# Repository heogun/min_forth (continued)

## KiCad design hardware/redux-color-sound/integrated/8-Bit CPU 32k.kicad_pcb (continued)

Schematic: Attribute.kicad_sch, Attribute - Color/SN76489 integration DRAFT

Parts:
R37, R38, R39, R40, R41: 470; R_Axial_DIN0207_L6.3mm_D2.5mm_P7.62mm_Horizontal
R42: 33; R_Axial_DIN0207_L6.3mm_D2.5mm_P7.62mm_Horizontal
U66: 74HC574; DIP-20_W7.62mm_Socket
U68: 74AC08; DIP-14_W7.62mm_Socket
U77: AS6C62256-55PCN ATTRIBUTE; DIP-28_W15.24mm_Socket
U78: 74HC283; DIP-16_W7.62mm_Socket
U79: 74HC86; DIP-14_W7.62mm_Socket
U80: 74HC245; DIP-20_W7.62mm_Socket
U81: 74HCT377; DIP-20_W7.62mm_Socket
U82: 74HC74; DIP-14_W7.62mm_Socket

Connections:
16MHz: U68.1, U68.2; also elsewhere on the board
+5V: U66.20 (VCC), U68.14 (VCC), U77.28 (VCC), U78.16 (VCC), U79.10, U79.14 (VCC), U80.1 (A->B), U80.20 (VCC), U81.20 (VCC), U82.4 (~S), U82.10 (~S), U82.14 (VCC); also elsewhere on the board
A9: U66.2 (D0); also elsewhere on the board
A10: U66.3 (D1); also elsewhere on the board
A11: U66.4 (D2); also elsewhere on the board
A12: U66.5 (D3); also elsewhere on the board
A13: U66.6 (D4); also elsewhere on the board
CS_16MHZ_DRV: R42.1, U68.3
CS_ACTIVE_LATCH: U79.9; also elsewhere on the board
CS_ATTR_D0: U77.11 (I/O0), U80.18 (B0), U81.3 (D0)
CS_ATTR_D1: U77.12 (I/O1), U80.17 (B1), U81.4 (D1)
CS_ATTR_D2: U77.13 (I/O2), U80.16 (B2), U81.7 (D2)
CS_ATTR_D3: U77.15 (I/O3), U80.15 (B3), U81.8 (D3)
CS_ATTR_D4: U77.16 (I/O4), U80.14 (B4), U81.13 (D4)
CS_ATTR_D5: U77.17 (I/O5), U80.13 (B5), U81.14 (D5)
CS_ATTR_D6: U77.18 (I/O6), U80.12 (B6), U81.17 (D6)
CS_ATTR_D7: U77.19 (I/O7), U80.11 (B7), U81.18 (D7)
CS_ATTR_MODE: U82.2 (D); also elsewhere on the board
CS_ATTR_Q0: U81.2 (Q0); also elsewhere on the board
CS_ATTR_Q1: U81.5 (Q1); also elsewhere on the board
CS_ATTR_Q2: U81.6 (Q2); also elsewhere on the board
CS_ATTR_Q3: U81.9 (Q3); also elsewhere on the board
CS_ATTR_Q4: U81.12 (Q4); also elsewhere on the board
CS_ATTR_Q5: U81.15 (Q5); also elsewhere on the board
CS_ATTR_Q6: U81.16 (Q6); also elsewhere on the board
CS_ATTR_Q7: U81.19 (Q7); also elsewhere on the board
CS_ATTR_WE_N: U77.27 (~WE); also elsewhere on the board
CS_CA6: R37.2, U66.19 (Q0), U77.4 (A6)
CS_CA7: R38.2, U66.18 (Q1), U77.3 (A7)
CS_CA8: R39.2, U66.17 (Q2), U77.25 (A8)
CS_CA9: R40.2, U66.16 (Q3), U77.24 (A9)
CS_CA10: R41.2, U66.15 (Q4), U77.21 (A10)
CS_EXT_16MHZ: R42.2, U81.11 (CP); also elsewhere on the board
CS_PENDING_ATTR: U82.5 (Q); also elsewhere on the board
CS_PENDING_BITMAP: U82.6 (~Q); also elsewhere on the board
CS_RGB_BLANK: U79.8; also elsewhere on the board
CS_ROW_CARRY: U78.9 (C4), U79.1
CS_SCA6: R37.1, U78.4 (S1)
CS_SCA7: R38.1, U78.1 (S2); also elsewhere on the board
CS_SCA8: R39.1, U78.13 (S3); also elsewhere on the board
CS_SCA9: R40.1, U78.10 (S4); also elsewhere on the board
CS_SCA10: R41.1, U79.3; also elsewhere on the board
CS_V4: U78.7 (C0); also elsewhere on the board
CS_V8: U78.5 (A1); also elsewhere on the board
CS_V16: U78.3 (A2); also elsewhere on the board
CS_V32: U78.14 (A3); also elsewhere on the board
CS_V64: U78.12 (A4); also elsewhere on the board
CS_V128: U79.2; also elsewhere on the board
CS_VA0: U77.10 (A0); also elsewhere on the board
CS_VA1: U77.9 (A1); also elsewhere on the board
CS_VA2: U77.8 (A2); also elsewhere on the board
CS_VA3: U77.7 (A3); also elsewhere on the board
CS_VA4: U77.6 (A4); also elsewhere on the board
CS_VA5: U77.5 (A5); also elsewhere on the board
CS_VDATA0: U80.2 (A0); also elsewhere on the board
CS_VDATA1: U80.3 (A1); also elsewhere on the board
CS_VDATA2: U80.4 (A2); also elsewhere on the board
CS_VDATA3: U80.5 (A3); also elsewhere on the board
CS_VDATA4: U80.6 (A4); also elsewhere on the board
CS_VDATA5: U80.7 (A5); also elsewhere on the board
CS_VDATA6: U80.8 (A6); also elsewhere on the board
CS_VDATA7: U80.9 (A7); also elsewhere on the board
CS_VREG_CP: U66.11 (Cp), U82.3 (C); also elsewhere on the board
GND: U66.7 (D5), U66.8 (D6), U66.9 (D7), U66.10 (GND), U68.4, U68.5, U68.7 (GND), U68.9, U68.10, U68.12, U68.13, U77.1 (A14), U77.2 (A12), U77.14 (GND), U77.20 (~CE), U77.23 (A11), U77.26 (A13), U78.2 (B2), U78.6 (B1), U78.8 (GND), U78.11 (B4), U78.15 (B3), U79.4, U79.5, U79.7 (GND), U79.12, U79.13, U80.10 (GND), U81.10 (GND), U82.7 (GND), U82.11 (C), U82.12 (D); also elsewhere on the board
~RESET: U82.1 (~R), U82.13 (~R); also elsewhere on the board
~VGA_GET: U77.22 (~OE), U81.1 (~E); also elsewhere on the board
~VREG_OE: U66.1 (OE), U80.19 (CE); also elsewhere on the board

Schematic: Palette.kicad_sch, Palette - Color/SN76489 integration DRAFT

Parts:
R28, R29: 750; R_Axial_DIN0207_L6.3mm_D2.5mm_P7.62mm_Horizontal
R30, R31, R32: 1.5k; R_Axial_DIN0207_L6.3mm_D2.5mm_P7.62mm_Horizontal
U83: 74HC173; DIP-16_W7.62mm_Socket
U84: 74HC08; DIP-14_W7.62mm_Socket
U85, U86: 74HC4002; DIP-14_W7.62mm_Socket
U87: 74HC30; DIP-14_W7.62mm_Socket
U88, U89: 74HC157; DIP-16_W7.62mm_Socket
U90: 74AC244; DIP-20_W7.62mm_Socket

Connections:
+5V: U83.16 (VCC), U84.14 (VCC), U85.14 (VDD), U86.14 (VDD), U87.6, U87.11, U87.12, U87.14 (VCC), U88.16 (VCC), U89.16 (VCC), U90.20 (VCC); also elsewhere on the board
CS_ACTIVE: U83.14 (D0), U86.13
CS_ACTIVE_LATCH: U83.3 (Q0); also elsewhere on the board
CS_ATTR_Q0: U88.3 (I1a); also elsewhere on the board
CS_ATTR_Q1: U88.6 (I1b); also elsewhere on the board
CS_ATTR_Q2: U88.10 (I1c); also elsewhere on the board
CS_ATTR_Q3: U88.13 (I1d); also elsewhere on the board
CS_ATTR_Q4: U88.2 (I0a); also elsewhere on the board
CS_ATTR_Q5: U88.5 (I0b); also elsewhere on the board
CS_ATTR_Q6: U88.11 (I0c); also elsewhere on the board
CS_ATTR_Q7: U88.14 (I0d); also elsewhere on the board
CS_B: U89.4 (Za), U90.11 (I0b)
CS_COLOR0: U88.4 (Za), U89.3 (I1a)
CS_COLOR1: U88.7 (Zb), U89.6 (I1b)
CS_COLOR2: U88.9 (Zc), U89.10 (I1c)
CS_COLOR3: U88.12 (Zd), U89.13 (I1d)
CS_COLOR_EN: U83.13 (D1); also elsewhere on the board
CS_COLOR_LATCH: U83.4 (Q1), U89.1 (S)
CS_DAC_B: R29.1, U90.9 (O0b)
CS_DAC_BI: R32.1, U90.7 (O1b)
CS_DAC_G: R28.1, U90.14 (O2a)
CS_DAC_GI: R31.1, U90.12 (O3a)
CS_DAC_R: U90.18 (O0a); also elsewhere on the board
CS_DAC_RI: R30.1, U90.16 (O1a)
CS_EXT_16MHZ: U83.7 (Cp); also elsewhere on the board
CS_G: U89.7 (Zb), U90.6 (I2a)
CS_H2: U87.5; also elsewhere on the board
CS_H4: U84.2, U87.4; also elsewhere on the board
CS_H8: U84.1, U87.3; also elsewhere on the board
CS_H12: U84.3, U85.11
CS_H16: U85.10, U87.2; also elsewhere on the board
CS_H32: U85.9, U87.1; also elsewhere on the board
CS_HHIGH_BAD: U86.1, U86.11
CS_HHIGH_OK: U86.2, U86.3, U86.4, U86.5, U87.8
CS_HLOW: U85.13, U86.10
CS_I: U89.12 (Zd), U90.4 (I1a), U90.8 (I3a), U90.13 (I1b)
CS_PIXEL: U88.1 (S), U89.2 (I0a), U89.5 (I0b), U89.11 (I0c), U89.14 (I0d); also elsewhere on the board
CS_R: U89.9 (Zc), U90.2 (I0a)
CS_RESET: U83.15 (Mr); also elsewhere on the board
CS_RGB_BLANK: U90.1 (OEa), U90.19 (OEb); also elsewhere on the board
CS_SCA7: U85.2; also elsewhere on the board
CS_SCA8: U85.3; also elsewhere on the board
CS_SCA9: U85.4; also elsewhere on the board
CS_SCA10: U85.5; also elsewhere on the board
CS_V256: U86.12; also elsewhere on the board
CS_VBAD: U85.1, U86.9
CS_VGA_B: R29.2, R32.2; also elsewhere on the board
CS_VGA_G: R28.2, R31.2; also elsewhere on the board
CS_VGA_R: R30.2; also elsewhere on the board
GND: U83.1 (Oe1), U83.2 (Oe2), U83.8 (GND), U83.10 (E2), U83.11 (D3), U83.12 (D2), U84.4, U84.5, U84.7 (GND), U84.9, U84.10, U84.12, U84.13, U85.7 (VSS), U85.12, U86.7 (VSS), U87.7 (GND), U88.8 (GND), U88.15 (E), U89.8 (GND), U89.15 (E), U90.10 (GND), U90.15 (I2b), U90.17 (I3b); also elsewhere on the board
~VGA_GET: U83.9 (E1); also elsewhere on the board

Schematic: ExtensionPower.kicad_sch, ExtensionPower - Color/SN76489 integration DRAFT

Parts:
C34, C35, C36, C37, C38, C39, C40, C41, C42, C44, C45, C46, C47, C48, C49, C50, C51, C52, C53, C54, C55, C56, C57, C58, C59, C60, C63: 100n; C_Disc_D5.0mm_W2.5mm_P2.50mm
C61: 10u 16V; CP_Radial_D5.0mm_P2.50mm

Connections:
+5V: C34.1, C35.1, C36.1, C37.1, C38.1, C39.1, C40.1, C41.1, C42.1, C44.1, C45.1, C46.1, C47.1, C48.1, C49.1, C50.1, C51.1, C52.1, C53.1, C54.1, C55.1, C56.1, C57.1, C58.1, C59.1, C60.1, C61.1, C63.1; also elsewhere on the board
GND: C34.2, C35.2, C36.2, C37.2, C38.2, C39.2, C40.2, C41.2, C42.2, C44.2, C45.2, C46.2, C47.2, C48.2, C49.2, C50.2, C51.2, C52.2, C53.2, C54.2, C55.2, C56.2, C57.2, C58.2, C59.2, C60.2, C61.2, C63.2; also elsewhere on the board

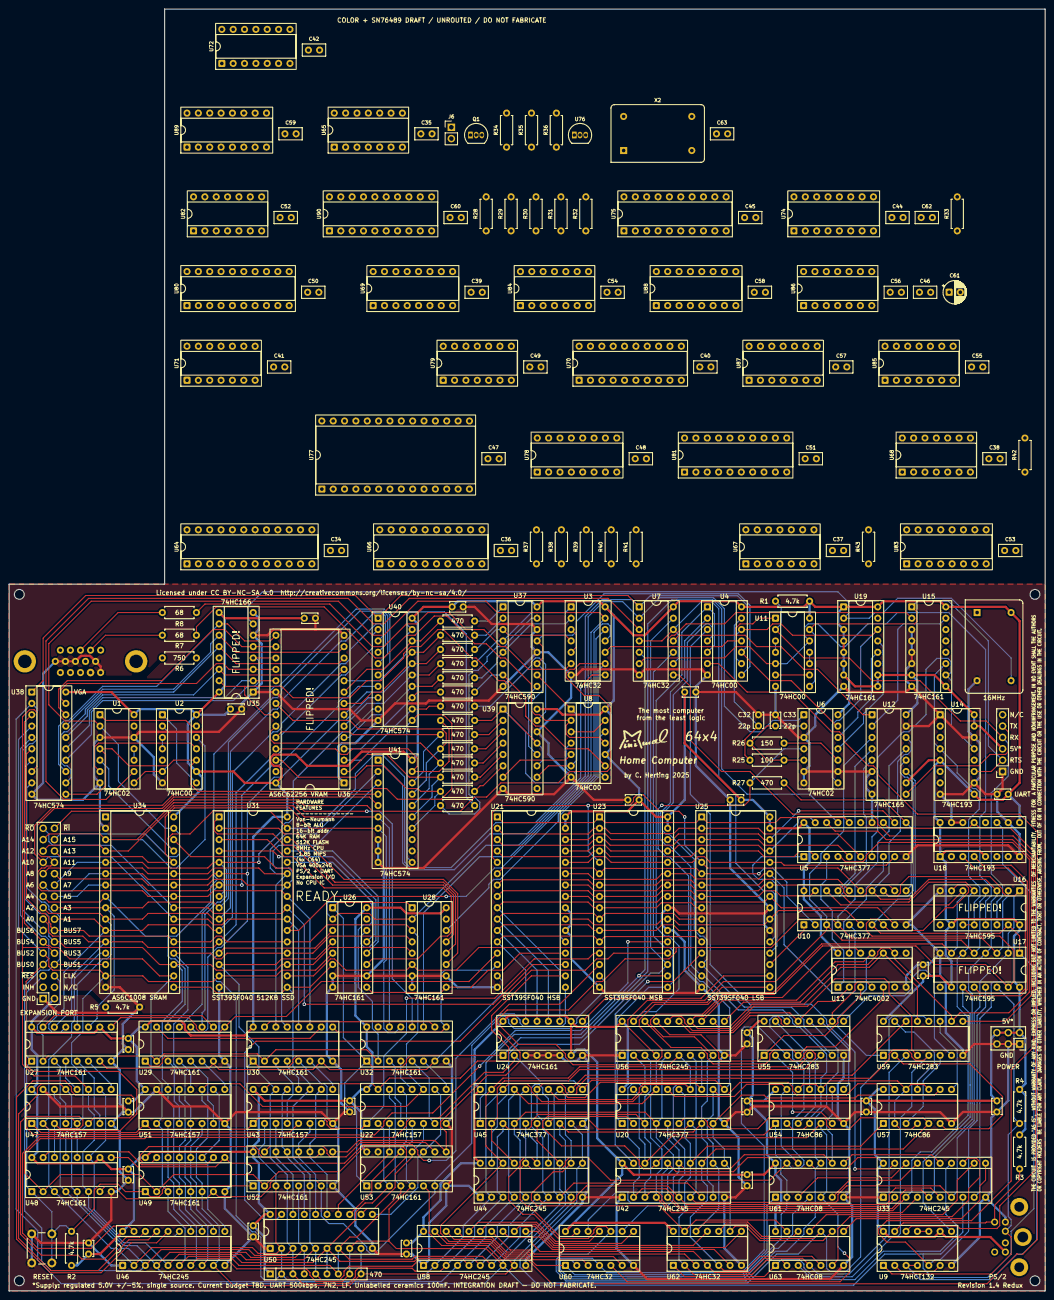
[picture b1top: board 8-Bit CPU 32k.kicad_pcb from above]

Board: 2 copper layers, 231.8 x 286.8 mm, 196 parts (0 on the bottom side), 348 nets.

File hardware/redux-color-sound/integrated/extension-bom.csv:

Reference,Value,Footprint,Schematic sheet
U64,ATF22V10C (CS_DECODE),Package_DIP:DIP-24_W7.62mm_Socket,ExtensionIO
U65,74HC04,Package_DIP:DIP-14_W7.62mm_Socket,ExtensionIO
U67,74HC02,Package_DIP:DIP-14_W7.62mm_Socket,ExtensionIO
U68,74AC08,Package_DIP:DIP-14_W7.62mm_Socket,Attribute
U69,74HC173,Package_DIP:DIP-16_W7.62mm_Socket,ExtensionIO
U70,74HC377,Package_DIP:DIP-20_W7.62mm_Socket,ExtensionIO
U71,74HC32,Package_DIP:DIP-14_W7.62mm_Socket,ExtensionIO
U72,74HC32,Package_DIP:DIP-14_W7.62mm_Socket,ExtensionIO
U74,SN76489AN,Package_DIP:DIP-16_W7.62mm_Socket,PSG
U75,74HCT244,Package_DIP:DIP-20_W7.62mm_Socket,PSG
U76,MCP130-450DI/TO,Package_TO_SOT_THT:TO-92_Inline,PSG
X2,3.579545MHz 5V FULL,Oscillator:Oscillator_DIP-14,PSG
U77,AS6C62256-55PCN ATTRIBUTE,Package_DIP:DIP-28_W15.24mm_Socket,Attribute
U78,74HC283,Package_DIP:DIP-16_W7.62mm_Socket,Attribute
U79,74HC86,Package_DIP:DIP-14_W7.62mm_Socket,Attribute
U66,74HC574,Package_DIP:DIP-20_W7.62mm_Socket,Attribute
U80,74HC245,Package_DIP:DIP-20_W7.62mm_Socket,Attribute
U81,74HCT377,Package_DIP:DIP-20_W7.62mm_Socket,Attribute
U82,74HC74,Package_DIP:DIP-14_W7.62mm_Socket,Attribute
U83,74HC173,Package_DIP:DIP-16_W7.62mm_Socket,Palette
U84,74HC08,Package_DIP:DIP-14_W7.62mm_Socket,Palette
U85,74HC4002,Package_DIP:DIP-14_W7.62mm_Socket,Palette
U86,74HC4002,Package_DIP:DIP-14_W7.62mm_Socket,Palette
U87,74HC30,Package_DIP:DIP-14_W7.62mm_Socket,Palette
U88,74HC157,Package_DIP:DIP-16_W7.62mm_Socket,Palette
U89,74HC157,Package_DIP:DIP-16_W7.62mm_Socket,Palette
U90,74AC244,Package_DIP:DIP-20_W7.62mm_Socket,Palette
R28,750,Resistor_THT:R_Axial_DIN0207_L6.3mm_D2.5mm_P7.62mm_Horizontal,Palette
R29,750,Resistor_THT:R_Axial_DIN0207_L6.3mm_D2.5mm_P7.62mm_Horizontal,Palette
R30,1.5k,Resistor_THT:R_Axial_DIN0207_L6.3mm_D2.5mm_P7.62mm_Horizontal,Palette
R31,1.5k,Resistor_THT:R_Axial_DIN0207_L6.3mm_D2.5mm_P7.62mm_Horizontal,Palette
R32,1.5k,Resistor_THT:R_Axial_DIN0207_L6.3mm_D2.5mm_P7.62mm_Horizontal,Palette
R42,33,Resistor_THT:R_Axial_DIN0207_L6.3mm_D2.5mm_P7.62mm_Horizontal,Attribute
R43,0 (SKEW TRIM),Resistor_THT:R_Axial_DIN0207_L6.3mm_D2.5mm_P7.62mm_Horizontal,ExtensionIO
R37,470,Resistor_THT:R_Axial_DIN0207_L6.3mm_D2.5mm_P7.62mm_Horizontal,Attribute
R38,470,Resistor_THT:R_Axial_DIN0207_L6.3mm_D2.5mm_P7.62mm_Horizontal,Attribute
R39,470,Resistor_THT:R_Axial_DIN0207_L6.3mm_D2.5mm_P7.62mm_Horizontal,Attribute
R40,470,Resistor_THT:R_Axial_DIN0207_L6.3mm_D2.5mm_P7.62mm_Horizontal,Attribute
R41,470,Resistor_THT:R_Axial_DIN0207_L6.3mm_D2.5mm_P7.62mm_Horizontal,Attribute
R33,4.7k,Resistor_THT:R_Axial_DIN0207_L6.3mm_D2.5mm_P7.62mm_Horizontal,PSG
R34,1k,Resistor_THT:R_Axial_DIN0207_L6.3mm_D2.5mm_P7.62mm_Horizontal,PSG
R35,10k,Resistor_THT:R_Axial_DIN0207_L6.3mm_D2.5mm_P7.62mm_Horizontal,PSG
R36,100k,Resistor_THT:R_Axial_DIN0207_L6.3mm_D2.5mm_P7.62mm_Horizontal,PSG
Q1,2N7000,Package_TO_SOT_THT:TO-92_Inline,PSG
J6,MONO LINE OUT / EXTERNAL AMP,Connector_PinHeader_2.54mm:PinHeader_1x02_P2.54mm_Vertical,PSG
C62,220n,Capacitor_THT:C_Disc_D5.0mm_W2.5mm_P2.50mm,PSG
C34,100n,Capacitor_THT:C_Disc_D5.0mm_W2.5mm_P2.50mm,ExtensionPower
C35,100n,Capacitor_THT:C_Disc_D5.0mm_W2.5mm_P2.50mm,ExtensionPower
C37,100n,Capacitor_THT:C_Disc_D5.0mm_W2.5mm_P2.50mm,ExtensionPower
C38,100n,Capacitor_THT:C_Disc_D5.0mm_W2.5mm_P2.50mm,ExtensionPower
C39,100n,Capacitor_THT:C_Disc_D5.0mm_W2.5mm_P2.50mm,ExtensionPower
C40,100n,Capacitor_THT:C_Disc_D5.0mm_W2.5mm_P2.50mm,ExtensionPower
C41,100n,Capacitor_THT:C_Disc_D5.0mm_W2.5mm_P2.50mm,ExtensionPower
C42,100n,Capacitor_THT:C_Disc_D5.0mm_W2.5mm_P2.50mm,ExtensionPower
C44,100n,Capacitor_THT:C_Disc_D5.0mm_W2.5mm_P2.50mm,ExtensionPower
C45,100n,Capacitor_THT:C_Disc_D5.0mm_W2.5mm_P2.50mm,ExtensionPower
C46,100n,Capacitor_THT:C_Disc_D5.0mm_W2.5mm_P2.50mm,ExtensionPower
C47,100n,Capacitor_THT:C_Disc_D5.0mm_W2.5mm_P2.50mm,ExtensionPower
C48,100n,Capacitor_THT:C_Disc_D5.0mm_W2.5mm_P2.50mm,ExtensionPower
C49,100n,Capacitor_THT:C_Disc_D5.0mm_W2.5mm_P2.50mm,ExtensionPower
C36,100n,Capacitor_THT:C_Disc_D5.0mm_W2.5mm_P2.50mm,ExtensionPower
C50,100n,Capacitor_THT:C_Disc_D5.0mm_W2.5mm_P2.50mm,ExtensionPower
C51,100n,Capacitor_THT:C_Disc_D5.0mm_W2.5mm_P2.50mm,ExtensionPower
C52,100n,Capacitor_THT:C_Disc_D5.0mm_W2.5mm_P2.50mm,ExtensionPower
C53,100n,Capacitor_THT:C_Disc_D5.0mm_W2.5mm_P2.50mm,ExtensionPower
C54,100n,Capacitor_THT:C_Disc_D5.0mm_W2.5mm_P2.50mm,ExtensionPower
C55,100n,Capacitor_THT:C_Disc_D5.0mm_W2.5mm_P2.50mm,ExtensionPower
C56,100n,Capacitor_THT:C_Disc_D5.0mm_W2.5mm_P2.50mm,ExtensionPower
C57,100n,Capacitor_THT:C_Disc_D5.0mm_W2.5mm_P2.50mm,ExtensionPower
C58,100n,Capacitor_THT:C_Disc_D5.0mm_W2.5mm_P2.50mm,ExtensionPower
C59,100n,Capacitor_THT:C_Disc_D5.0mm_W2.5mm_P2.50mm,ExtensionPower
C60,100n,Capacitor_THT:C_Disc_D5.0mm_W2.5mm_P2.50mm,ExtensionPower
C61,10u 16V,Capacitor_THT:CP_Radial_D5.0mm_P2.50mm,ExtensionPower
C63,100n,Capacitor_THT:C_Disc_D5.0mm_W2.5mm_P2.50mm,ExtensionPower

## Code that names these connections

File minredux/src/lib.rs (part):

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pub const FI: u32 = 1 << 6;
pub const IO: u32 = 1 << 7;
pub const MC: u32 = 1 << 8;
pub const CIH: u32 = 1 << 9;
pub const CE: u32 = 1 << 10;
pub const BI: u32 = 1 << 11;
pub const AI: u32 = 1 << 12;
pub const AO: u32 = 1 << 13;
pub const COH: u32 = 1 << 14;
pub const COL: u32 = 1 << 15;
pub const MIL: u32 = 1 << 16;
pub const MIH: u32 = 1 << 17;
pub const ME: u32 = 1 << 18;
pub const CIL: u32 = 1 << 19;
pub const MZ: u32 = 1 << 20;
pub const RO: u32 = 1 << 21;
pub const NI: u32 = 1 << 22;
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
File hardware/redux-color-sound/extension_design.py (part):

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    return parts, gates


# ATF22V10C (U64) pin map and equations.  Products are lists of (net, level);
# an output is active-low when its flag is True (pin low while the sum is true).
PLD_ADDRESS_PINS = {1: 4, 2: 5, 3: 6, 4: 7, 5: 8, 6: 9, 7: 10, 8: 11, 9: 12, 10: 13,
                    11: 14, 13: 15, 14: 0, 15: 1, 16: 2}
PLD_IO_PINS = {17: ('CS_ATTR_MODE', 'in'), 18: ('CS_INH_EXT', 'in'), 19: ('CS_RI_N', 'in'),
               20: ('CS_SND_EN_N', 'out'), 21: ('CS_CTRL_SEL_N', 'out'),
               22: ('CS_STATUS_SEL_N', 'out'), 23: ('CS_RAM_INH', 'out')}
_HIT = [(f'CS_A{i}', True) for i in range(15, 8, -1)] + [('CS_A8', False)] + \
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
